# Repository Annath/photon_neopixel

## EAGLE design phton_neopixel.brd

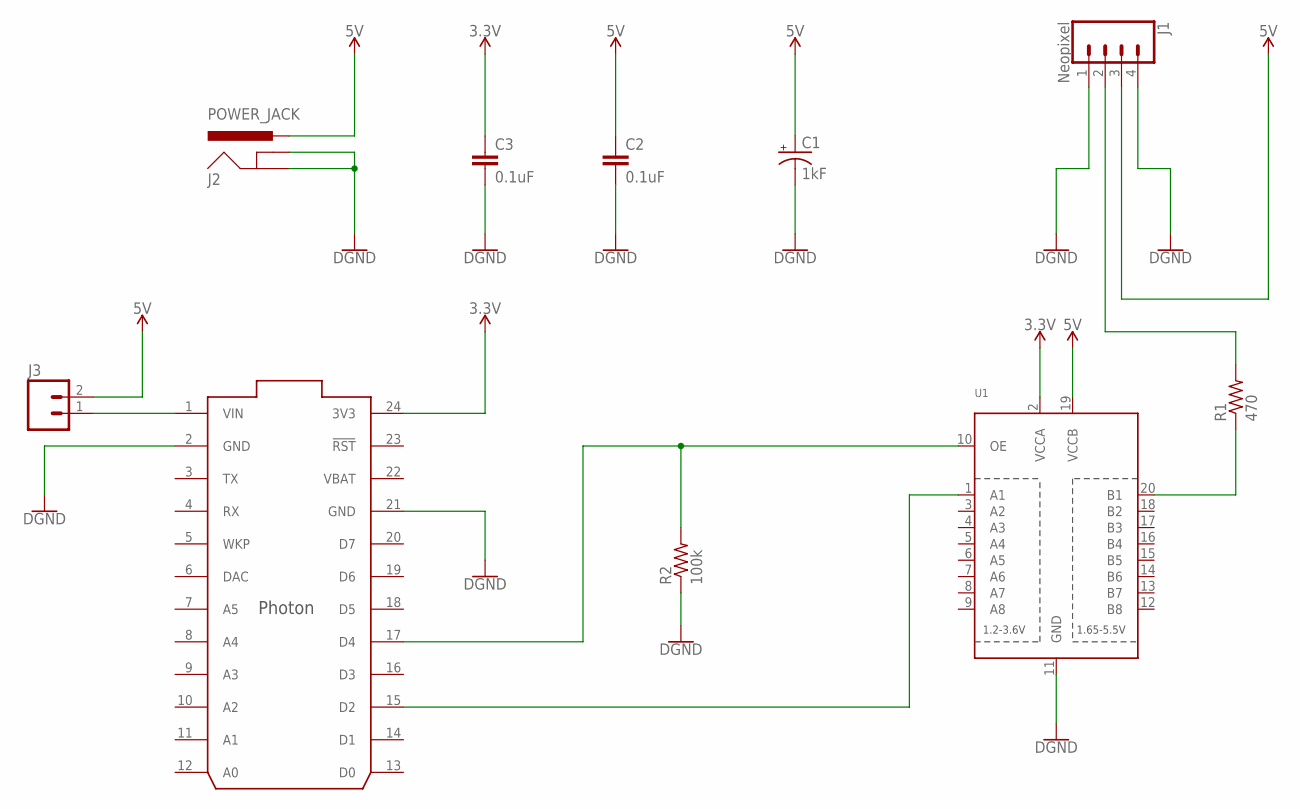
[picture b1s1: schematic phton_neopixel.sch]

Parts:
C1: 1kF; CPOL-RADIAL-5MM-10MM
C2, C3: 0.1uF; 0603-CAP
J1: Neopixel; 1X04
J2: POWER_JACK; POWER_JACK_PTH
J3: M02PTH; 1X02
R1: 470; 0207/7
R2: 100k; 0207/7
U1: TXB0108PWR; TSSOP20
U2: PHOTON_WITH_HEADERS; PHOTON

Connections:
3.3V: C3.1, U1.2 (VCCA), U2.24 (3V3)
5V: C1.+, C2.1, J1.3, J2.PWR, J3.2, U1.19 (VCCB)
GND: C1.-, C2.2, C3.2, J1.1, J1.4, J2.GND, J2.GNDBREAK, R2.1, U1.11 (GND), U2.2 (GND), U2.21 (GND)
unnamed: R1.1, U1.20 (B1)
unnamed: J3.1, U2.1 (VIN)
unnamed: R2.2, U1.10 (OE), U2.17 (D4)
unnamed: J1.2, R1.2
unnamed: U1.1 (A1), U2.15 (D2)
VBAT: U2.22 (VBAT)

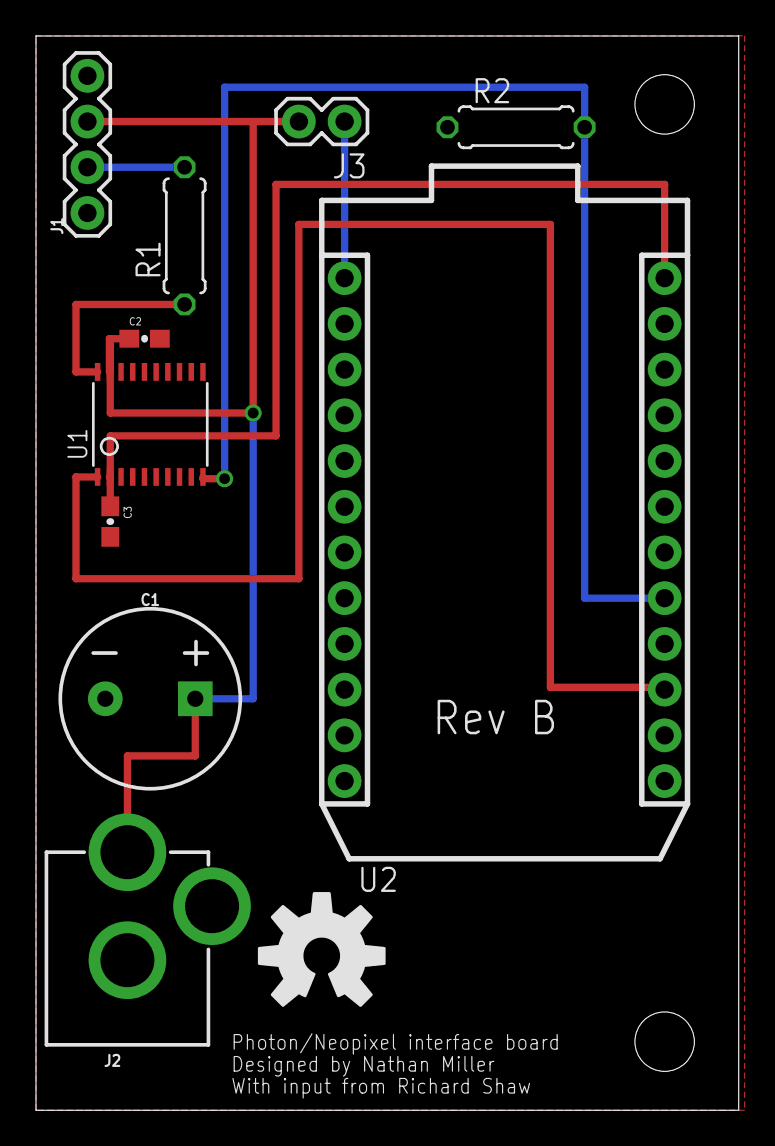
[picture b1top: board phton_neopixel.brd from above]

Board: 2 copper layers, 39.0 x 59.7 mm, 13 parts (0 on the bottom side), 8 nets.

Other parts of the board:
U$1: OSHW-LOGO-L
U$2, U$3: STAND-OFF

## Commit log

2017-12-07 Added DRU
2017-12-12 Added filter caps and cleaned up the layout a lot
2017-12-13 Added jumper for 5V to the photon, improved routing and naming
2017-12-13 Removed unnecessary trace
2017-12-13 Changed pull-down resistor to 100k

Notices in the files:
parts and their libraries:
SparkFun-Capacitors: Licensing: Creative Commons ShareAlike 4.0 International - https://creativecommons.org/licenses/by-sa/4.0
